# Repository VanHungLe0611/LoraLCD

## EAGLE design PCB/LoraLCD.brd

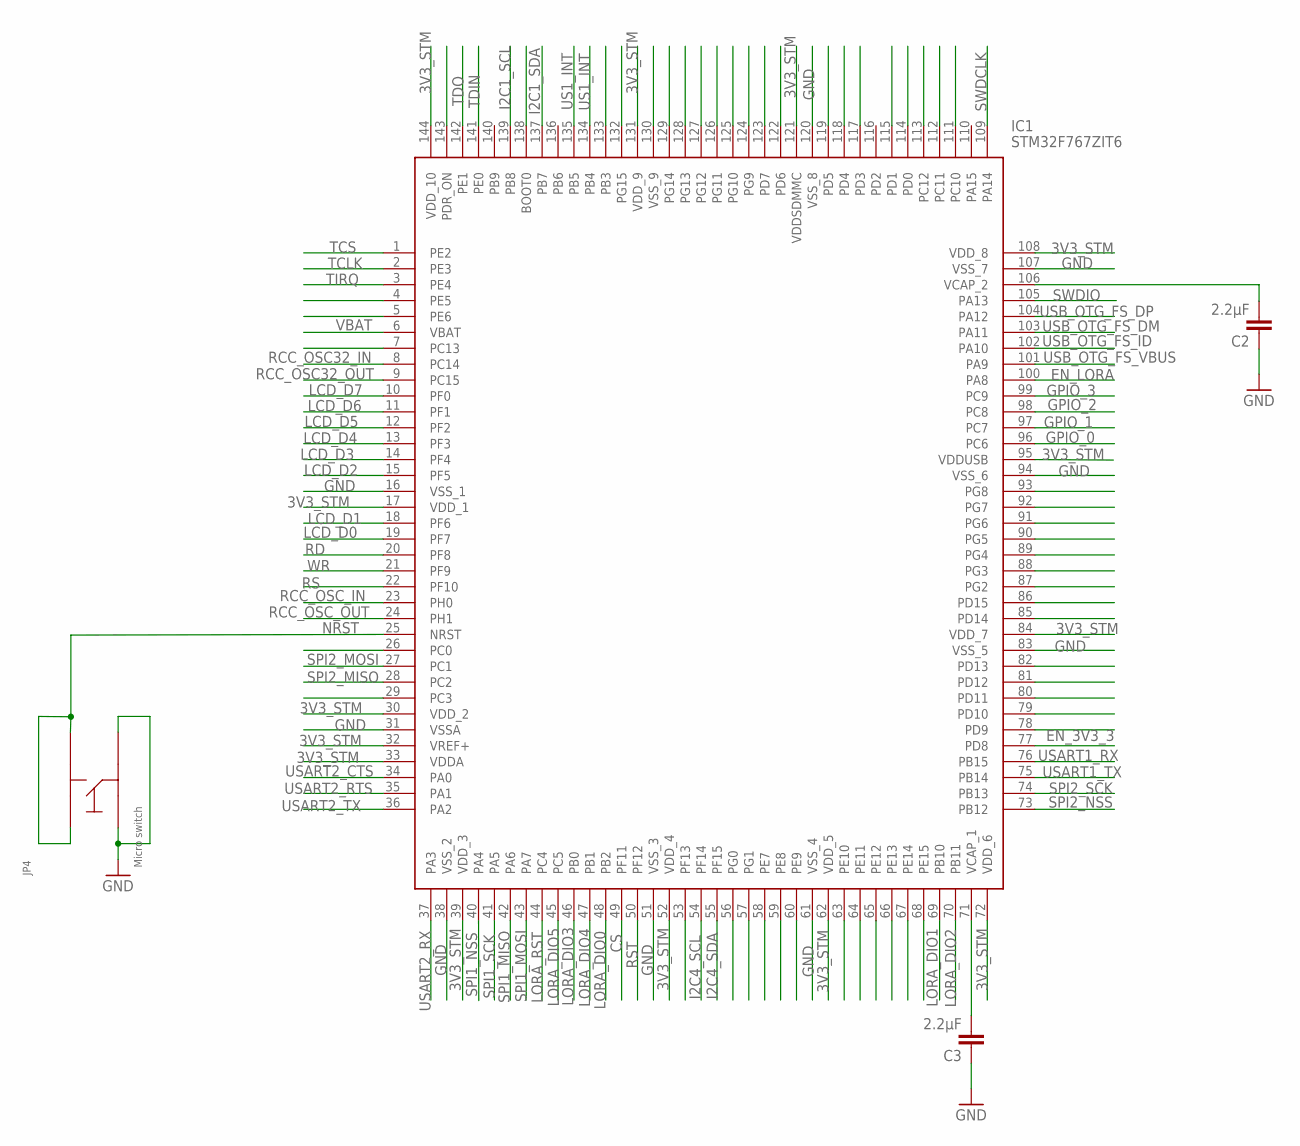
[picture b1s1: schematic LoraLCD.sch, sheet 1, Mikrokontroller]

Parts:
C2, C3: 2.2µF; C0402K
IC1: STM32F767ZIT6; QFP50P2200X2200X160-144N
JP4: MICRO_SWITCH_6MM; SKQGADE010; MPN SKQGADE010

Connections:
3V3_STM: IC1.17 (VDD_1), IC1.30 (VDD_2), IC1.32 (VREF+), IC1.33 (VDDA), IC1.39 (VDD_3), IC1.52 (VDD_4), IC1.62 (VDD_5), IC1.72 (VDD_6), IC1.84 (VDD_7), IC1.95 (VDDUSB), IC1.108 (VDD_8), IC1.121 (VDDSDMMC), IC1.131 (VDD_9), IC1.144 (VDD_10); also elsewhere on the board
CS: IC1.49 (PF11); also elsewhere on the board
EN_3V3_3: IC1.77 (PD8); also elsewhere on the board
EN_LORA: IC1.100 (PA8); also elsewhere on the board
GND: C2.1, C3.1, IC1.16 (VSS_1), IC1.31 (VSSA), IC1.38 (VSS_2), IC1.51 (VSS_3), IC1.61 (VSS_4), IC1.83 (VSS_5), IC1.94 (VSS_6), IC1.107 (VSS_7), IC1.120 (VSS_8), JP4.P$3, JP4.P$4; also elsewhere on the board
GPIO_0: IC1.96 (PC6); also elsewhere on the board
GPIO_1: IC1.97 (PC7); also elsewhere on the board
GPIO_2: IC1.98 (PC8); also elsewhere on the board
GPIO_3: IC1.99 (PC9); also elsewhere on the board
I2C1_SCL: IC1.139 (PB8); also elsewhere on the board
I2C1_SDA: IC1.137 (PB7); also elsewhere on the board
I2C4_SCL: IC1.54 (PF14); also elsewhere on the board
I2C4_SDA: IC1.55 (PF15); also elsewhere on the board
LCD_D0: IC1.19 (PF7); also elsewhere on the board
LCD_D1: IC1.18 (PF6); also elsewhere on the board
LCD_D2: IC1.15 (PF5); also elsewhere on the board
LCD_D3: IC1.14 (PF4); also elsewhere on the board
LCD_D4: IC1.13 (PF3); also elsewhere on the board
LCD_D5: IC1.12 (PF2); also elsewhere on the board
LCD_D6: IC1.11 (PF1); also elsewhere on the board
LCD_D7: IC1.10 (PF0); also elsewhere on the board
LORA_DIO0: IC1.48 (PB2); also elsewhere on the board
LORA_DIO1: IC1.69 (PB10); also elsewhere on the board
LORA_DIO2: IC1.70 (PB11); also elsewhere on the board
LORA_DIO3: IC1.46 (PB0); also elsewhere on the board
LORA_DIO4: IC1.47 (PB1); also elsewhere on the board
LORA_DIO5: IC1.45 (PC5); also elsewhere on the board
LORA_RST: IC1.44 (PC4); also elsewhere on the board
unnamed: C2.2, IC1.106 (VCAP_2)
unnamed: C3.2, IC1.71 (VCAP_1)
NRST: IC1.25 (NRST), JP4.P$1, JP4.P$2; also elsewhere on the board
RCC_OSC32_IN: IC1.8 (PC14); also elsewhere on the board
RCC_OSC32_OUT: IC1.9 (PC15); also elsewhere on the board
RCC_OSC_IN: IC1.23 (PH0); also elsewhere on the board
RCC_OSC_OUT: IC1.24 (PH1); also elsewhere on the board
RD: IC1.20 (PF8); also elsewhere on the board
RS: IC1.22 (PF10); also elsewhere on the board
RST: IC1.50 (PF12); also elsewhere on the board
SPI1_MISO: IC1.42 (PA6); also elsewhere on the board
SPI1_MOSI: IC1.43 (PA7); also elsewhere on the board
SPI1_NSS: IC1.40 (PA4); also elsewhere on the board
SPI1_SCK: IC1.41 (PA5); also elsewhere on the board
SPI2_MISO: IC1.28 (PC2); also elsewhere on the board
SPI2_MOSI: IC1.27 (PC1); also elsewhere on the board
SPI2_NSS: IC1.73 (PB12); also elsewhere on the board
SPI2_SCK: IC1.74 (PB13); also elsewhere on the board
SWDCLK: IC1.109 (PA14); also elsewhere on the board
SWDIO: IC1.105 (PA13); also elsewhere on the board
TCLK: IC1.2 (PE3); also elsewhere on the board
TCS: IC1.1 (PE2); also elsewhere on the board
TDIN: IC1.141 (PE0); also elsewhere on the board
TDO: IC1.142 (PE1); also elsewhere on the board
TIRQ: IC1.3 (PE4); also elsewhere on the board
US1_INT: IC1.134 (PB4), IC1.135 (PB5); also elsewhere on the board
USART1_RX: IC1.76 (PB15); also elsewhere on the board
USART1_TX: IC1.75 (PB14); also elsewhere on the board
USART2_CTS: IC1.34 (PA0); also elsewhere on the board
USART2_RTS: IC1.35 (PA1); also elsewhere on the board
USART2_RX: IC1.37 (PA3); also elsewhere on the board
USART2_TX: IC1.36 (PA2); also elsewhere on the board
USB_OTG_FS_DM: IC1.103 (PA11); also elsewhere on the board
USB_OTG_FS_DP: IC1.104 (PA12); also elsewhere on the board
USB_OTG_FS_ID: IC1.102 (PA10); also elsewhere on the board
USB_OTG_FS_VBUS: IC1.101 (PA9); also elsewhere on the board
VBAT: IC1.6 (VBAT); also elsewhere on the board
WR: IC1.21 (PF9); also elsewhere on the board

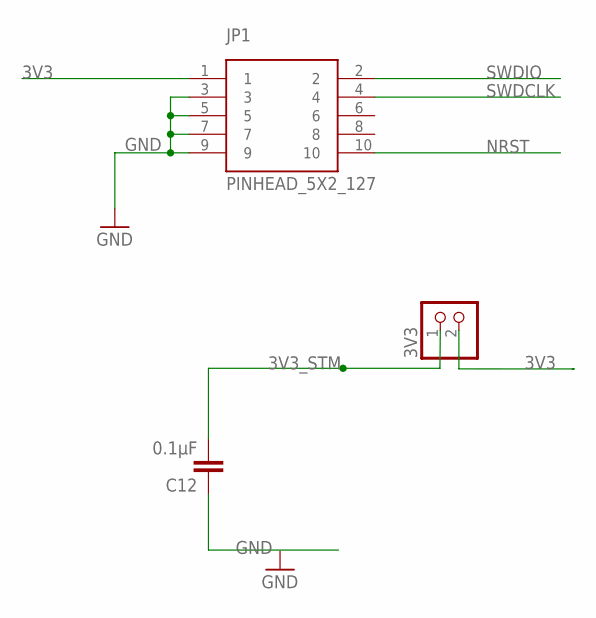
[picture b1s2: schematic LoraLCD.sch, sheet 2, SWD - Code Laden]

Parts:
3V3: PINHD-1X2; 1X02
C12: 0.1µF; C0402K
JP1: PINHEAD_5X2_127; PINHEAD_2X5_127

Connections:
3V3: 3V3.2, JP1.1; also elsewhere on the board
3V3_STM: 3V3.1, C12.2; also elsewhere on the board
GND: C12.1, JP1.3, JP1.5, JP1.7, JP1.9; also elsewhere on the board
NRST: JP1.10; also elsewhere on the board
SWDCLK: JP1.4; also elsewhere on the board
SWDIO: JP1.2; also elsewhere on the board

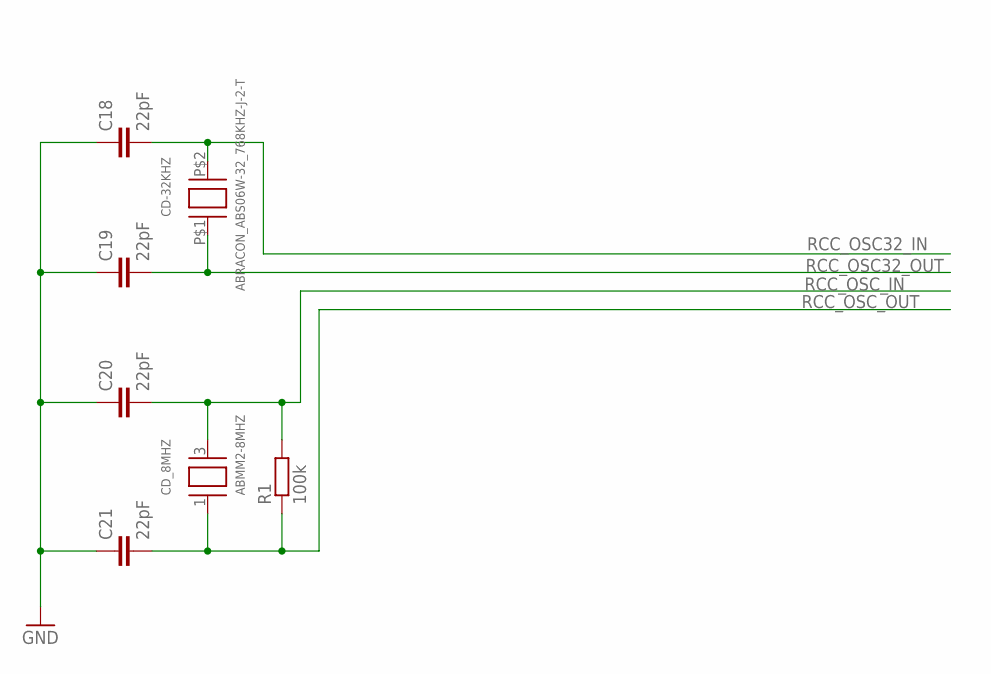
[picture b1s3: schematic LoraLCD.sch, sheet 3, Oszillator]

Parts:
C18, C19, C20, C21: 22pF; C0402K
CD-32KHZ: ABRACON_ABS06W-32_768KHZ-J-2-T; 2MM_X_1_2MM
CD_8MHZ: ABMM2-8MHZ; CRYSTAL_ABRACON_6MM_3.6MM
R1: 100k; C0402K

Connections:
GND: C18.1, C19.1, C20.1, C21.1; also elsewhere on the board
RCC_OSC32_IN: C18.2, CD-32KHZ.P$2 (C1); also elsewhere on the board
RCC_OSC32_OUT: C19.2, CD-32KHZ.P$1 (C0); also elsewhere on the board
RCC_OSC_IN: C20.2, CD_8MHZ.3 (C1), R1.2; also elsewhere on the board
RCC_OSC_OUT: C21.2, CD_8MHZ.1 (C0), R1.1; also elsewhere on the board

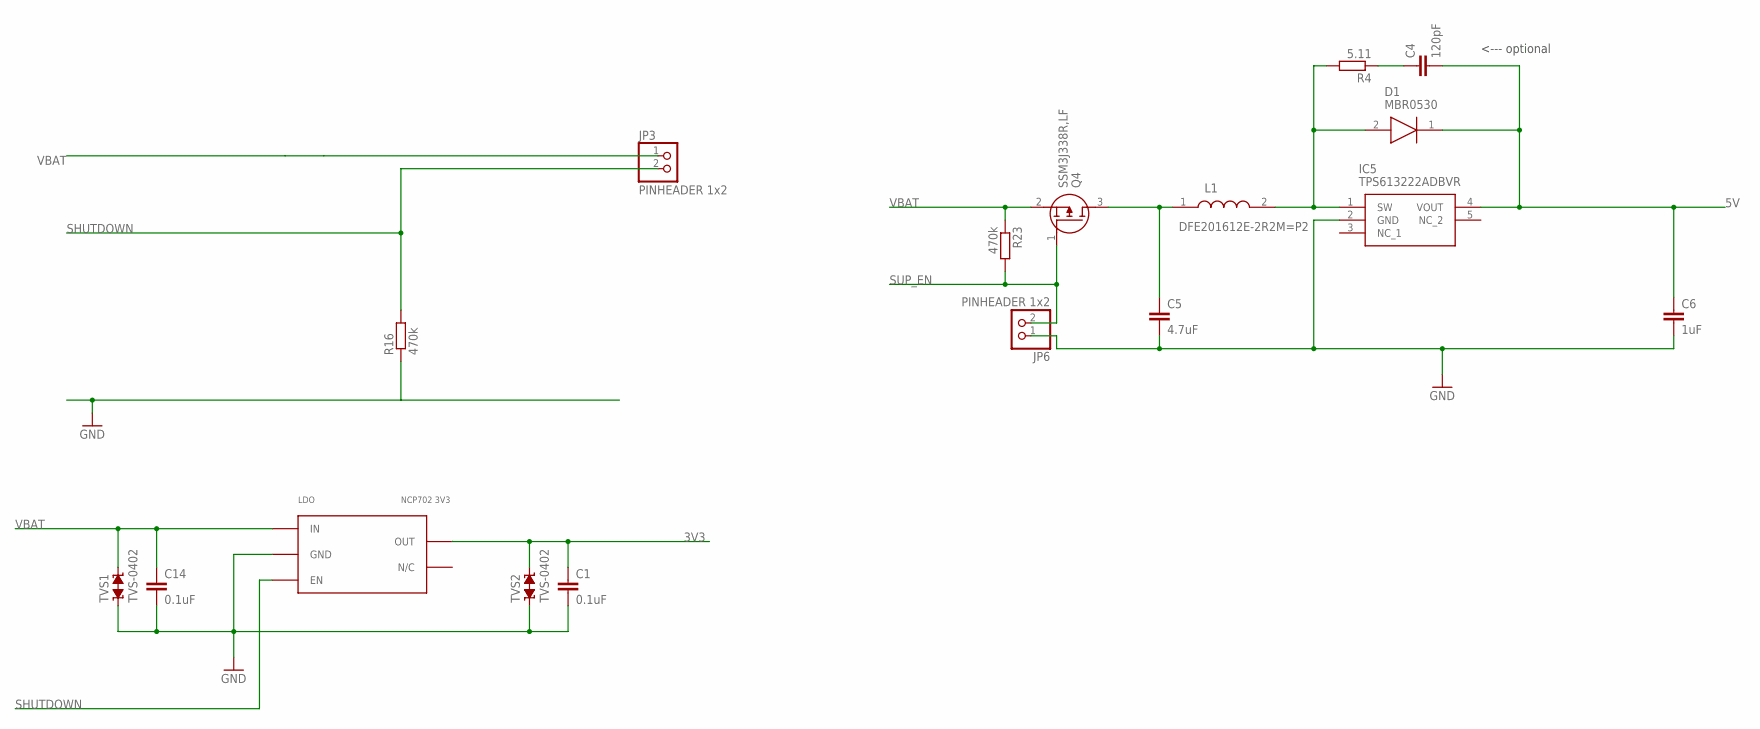
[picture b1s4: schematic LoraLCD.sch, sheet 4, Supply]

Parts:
C1: 0.1uF; C0402K; MPN CCC-23
C4: 120pF; C0402K; MPN GRM1555C1H121JA01D
C5: 4.7uF; C0603K; MPN JMK107BB7475KA-T
C6: 1uF; C0603K
C14: 0.1uF; C0402K
D1: MBR0530; SOD3716X135N
IC5: TPS613222ADBVR; SOT95P280X145-5N
JP3, JP6: PINHEADER 1x2; 1X02
L1: DFE201612E-2R2M=P2; INDC2016X120N
LDO: NCP702 3V3; SOT563; MPN NCP702SN33T1G
Q4: SSM3J338R,LF; SSM3J332RLFT
R4: 5.11; R0402; MPN RC0402FR-132M2L
R16, R23: 470k; R0402
TVS1, TVS2: TVS-0402; TVS0402; MPN PESD0402-140

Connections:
3V3: C1.1, LDO.P$5 (OUT), TVS2.2; also elsewhere on the board
5V: C4.2, C6.1, D1.1 (K), IC5.4 (VOUT); also elsewhere on the board
GND: C1.2, C5.2, C6.2, C14.2, IC5.2 (GND), JP6.1, LDO.P$2 (GND), R16.1, TVS1.1, TVS2.1; also elsewhere on the board
unnamed: D1.2 (A), IC5.1 (SW), L1.2, R4.2
unnamed: C4.1, R4.1
unnamed: C5.1, L1.1, Q4.3 (D)
SHUTDOWN: JP3.2, LDO.P$3 (EN), R16.2
SUP_EN: JP6.2, Q4.1 (G), R23.2
VBAT: C14.1, JP3.1, LDO.P$1 (IN), Q4.2 (S), R23.1, TVS1.2; also elsewhere on the board

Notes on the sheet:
<--- optional

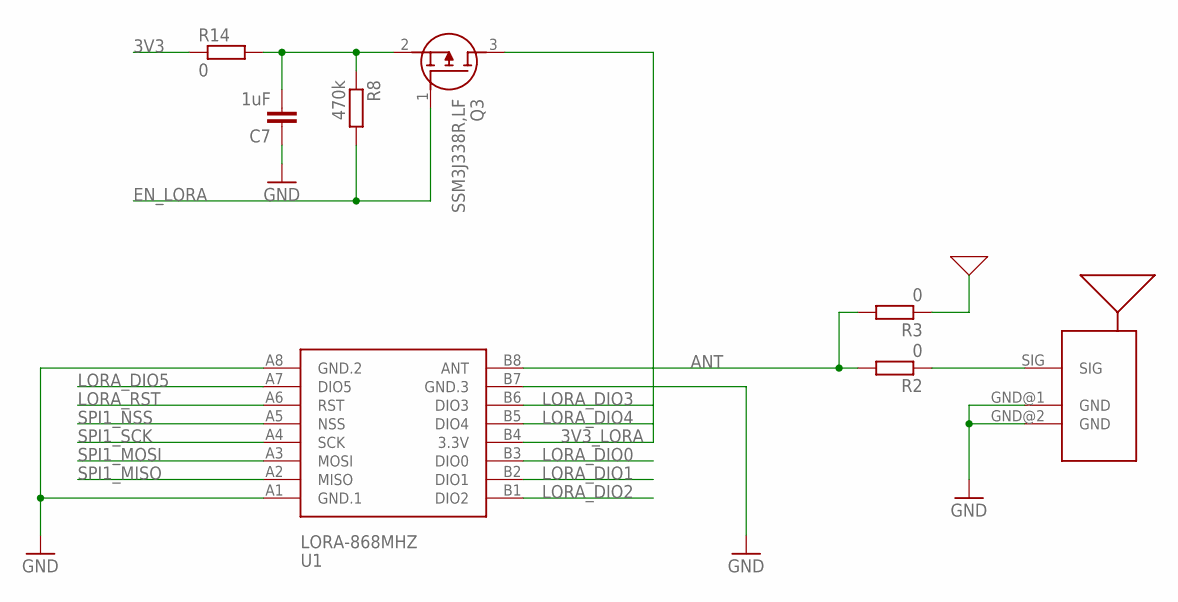
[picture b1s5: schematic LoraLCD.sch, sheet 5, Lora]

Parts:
ANT1: U.FL-R-SMT-1; UFL_HIROSE; MPN U.FL-R-SMT-1(10)
C7: 1uF; C0402K
Q3: SSM3J338R,LF; SSM3J332RLFT
R2, R3: 0; C0402K
R8: 470k; R0402
R14: 0; R0402
U1: LORA-868MHZ; WIRELESS-LORA-RFM95W#SMD

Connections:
3V3: R14.1; also elsewhere on the board
3V3_LORA: Q3.3 (D), U1.B4 (3.3V)
ANT: R2.2, R3.2, U1.B8 (ANT)
EN_LORA: Q3.1 (G), R8.2; also elsewhere on the board
GND: ANT1.GND@1 (GND), ANT1.GND@2 (GND), C7.1, U1.A1 (GND.1), U1.A8 (GND.2), U1.B7 (GND.3); also elsewhere on the board
HELIX_ANT: R3.1
LORA_DIO0: U1.B3 (DIO0); also elsewhere on the board
LORA_DIO1: U1.B2 (DIO1); also elsewhere on the board
LORA_DIO2: U1.B1 (DIO2); also elsewhere on the board
LORA_DIO3: U1.B6 (DIO3); also elsewhere on the board
LORA_DIO4: U1.B5 (DIO4); also elsewhere on the board
LORA_DIO5: U1.A7 (DIO5); also elsewhere on the board
LORA_RST: U1.A6 (RST); also elsewhere on the board
unnamed: ANT1.SIG, R2.1
unnamed: C7.2, Q3.2 (S), R8.1, R14.2
SPI1_MISO: U1.A2 (MISO); also elsewhere on the board
SPI1_MOSI: U1.A3 (MOSI); also elsewhere on the board
SPI1_NSS: U1.A5 (NSS); also elsewhere on the board
SPI1_SCK: U1.A4 (SCK); also elsewhere on the board

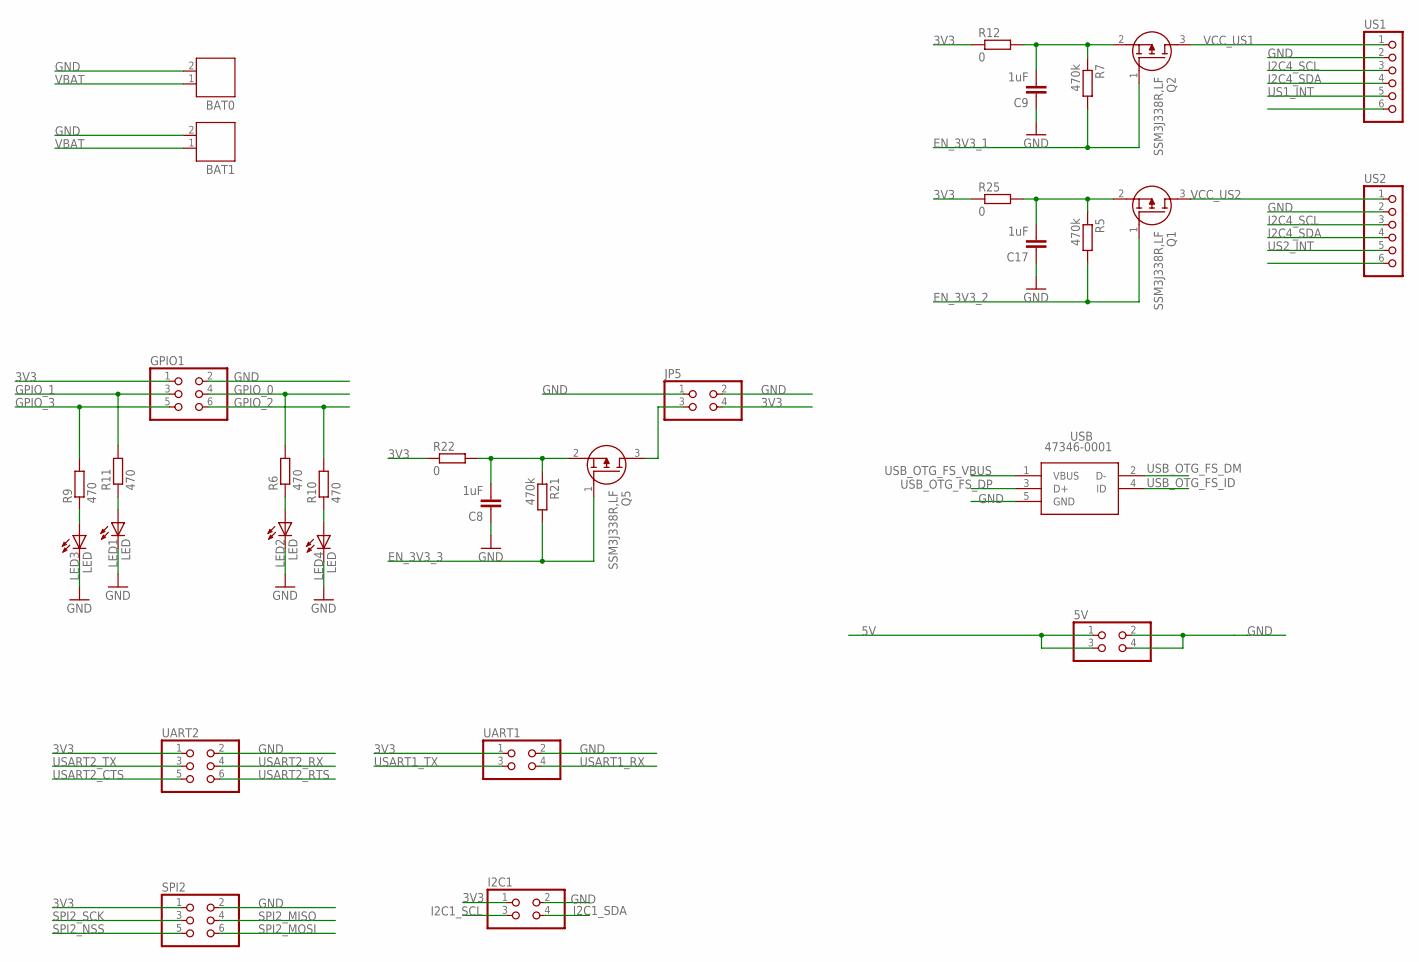
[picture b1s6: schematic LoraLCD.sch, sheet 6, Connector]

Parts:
5V: PINHD-2X2; 2X02
BAT0, BAT1: JST-PH2; MPN B2B-PH-K-S
C8, C9, C17: 1uF; C0402K
GPIO1: PINHD-2X3; 2X03
I2C1: PINHD-2X2; 2X02
JP5: PINHD-2X2; 2X02
LED1, LED2, LED3, LED4: LED; 0603_AK
Q1, Q2, Q5: SSM3J338R,LF; SSM3J332RLFT
R5, R7, R21: 470k; R0402
R6, R9, R10, R11: 470; R0402
R12, R22, R25: 0; R0402
SPI2: PINHD-2X3; 2X03
UART1: PINHD-2X2; 2X02
UART2: PINHD-2X3; 2X03
US1, US2: PINHD-1X6; 1X06
USB: 47346-0001

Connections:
3V3: GPIO1.1, I2C1.1, JP5.4, R12.1, R22.1, R25.1, SPI2.1, UART1.1, UART2.1; also elsewhere on the board
5V: 5V.1, 5V.3; also elsewhere on the board
EN_3V3_1: Q2.1 (G), R7.2
EN_3V3_2: Q1.1 (G), R5.2
EN_3V3_3: Q5.1 (G), R21.2; also elsewhere on the board
GND: 5V.2, 5V.4, BAT0.2, BAT1.2, C8.1, C9.1, C17.1, GPIO1.2, I2C1.2, JP5.1, JP5.2, LED1.K (C), LED2.K (C), LED3.K (C), LED4.K (C), SPI2.2, UART1.2, UART2.2, US1.2, US2.2, USB.5 (GND); also elsewhere on the board
GPIO_0: GPIO1.4, R6.2; also elsewhere on the board
GPIO_1: GPIO1.3, R11.2; also elsewhere on the board
GPIO_2: GPIO1.6, R10.2; also elsewhere on the board
GPIO_3: GPIO1.5, R9.2; also elsewhere on the board
I2C1_SCL: I2C1.3; also elsewhere on the board
I2C1_SDA: I2C1.4; also elsewhere on the board
I2C4_SCL: US1.3, US2.3; also elsewhere on the board
I2C4_SDA: US1.4, US2.4; also elsewhere on the board
unnamed: LED1.A, R11.1
unnamed: LED2.A, R6.1
unnamed: C17.2, Q1.2 (S), R5.1, R25.2
unnamed: LED3.A, R9.1
unnamed: LED4.A, R10.1
unnamed: C8.2, Q5.2 (S), R21.1, R22.2
unnamed: JP5.3, Q5.3 (D)
unnamed: C9.2, Q2.2 (S), R7.1, R12.2
PS: US1.6
SPI2_MISO: SPI2.4; also elsewhere on the board
SPI2_MOSI: SPI2.6; also elsewhere on the board
SPI2_NSS: SPI2.5; also elsewhere on the board
SPI2_SCK: SPI2.3; also elsewhere on the board
US1_INT: US1.5; also elsewhere on the board
US2_INT: US2.5
USART1_RX: UART1.4; also elsewhere on the board
USART1_TX: UART1.3; also elsewhere on the board
USART2_CTS: UART2.5; also elsewhere on the board
USART2_RTS: UART2.6; also elsewhere on the board
USART2_RX: UART2.4; also elsewhere on the board
USART2_TX: UART2.3; also elsewhere on the board
USB_OTG_FS_DM: USB.2 (D-); also elsewhere on the board
USB_OTG_FS_DP: USB.3 (D+); also elsewhere on the board
USB_OTG_FS_ID: USB.4 (ID); also elsewhere on the board
USB_OTG_FS_VBUS: USB.1 (VBUS); also elsewhere on the board
VBAT: BAT0.1, BAT1.1; also elsewhere on the board
VCC_US1: Q2.3 (D), US1.1
VCC_US2: Q1.3 (D), US2.1

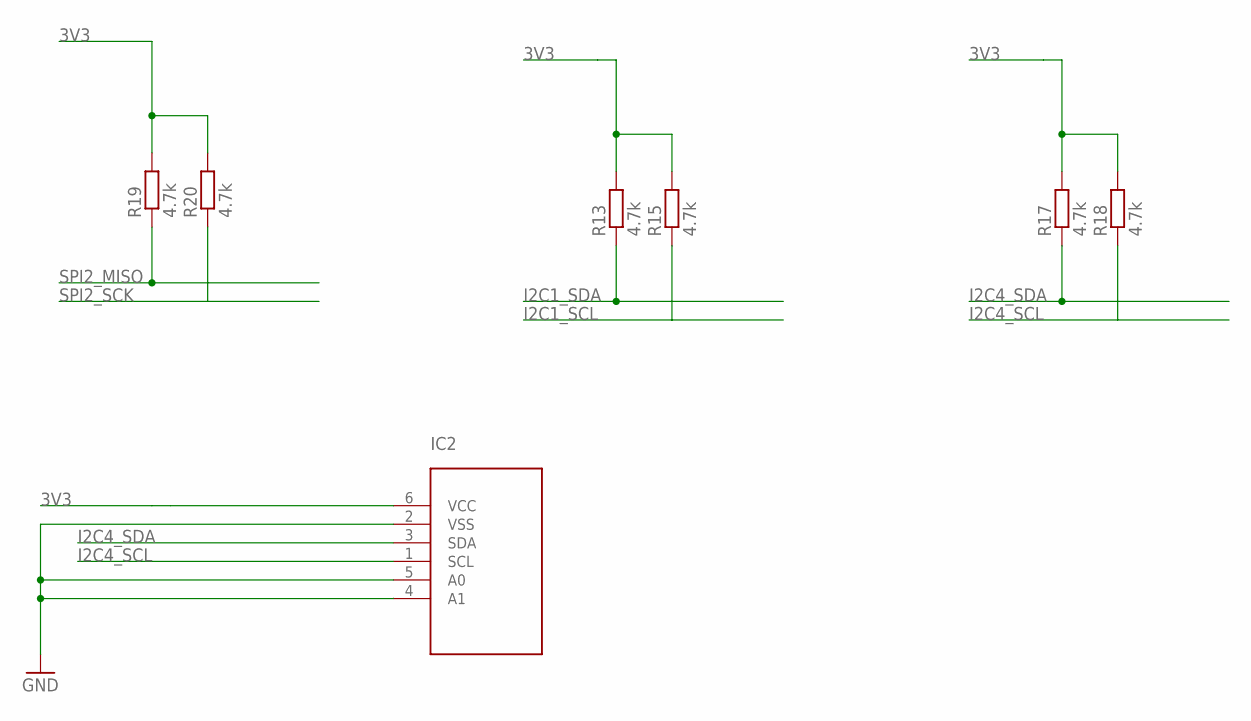
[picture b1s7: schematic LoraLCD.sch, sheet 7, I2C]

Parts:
IC2: 24AA025E64T-I/OT; SOT23-6; MPN 24AA025E64T-I/OT
R13, R15, R17, R18, R19, R20: 4.7k; C0402K

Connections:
3V3: IC2.6 (VCC), R13.2, R15.2, R17.2, R18.2, R19.2, R20.2; also elsewhere on the board
GND: IC2.2 (VSS), IC2.4 (A1), IC2.5 (A0); also elsewhere on the board
I2C1_SCL: R15.1; also elsewhere on the board
I2C1_SDA: R13.1; also elsewhere on the board
I2C4_SCL: IC2.1 (SCL), R18.1; also elsewhere on the board
I2C4_SDA: IC2.3 (SDA), R17.1; also elsewhere on the board
SPI2_MISO: R19.1; also elsewhere on the board
SPI2_SCK: R20.1; also elsewhere on the board

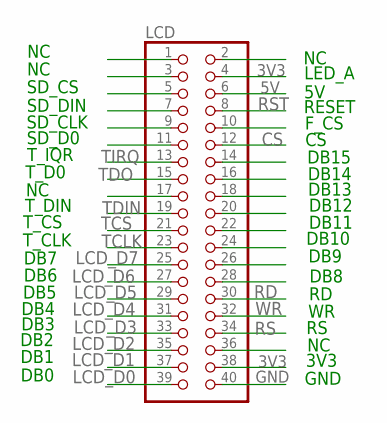
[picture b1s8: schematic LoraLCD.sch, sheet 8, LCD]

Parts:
LCD: PINHD-2X20; 2X20

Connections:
3V3: LCD.4, LCD.38; also elsewhere on the board
5V: LCD.6; also elsewhere on the board
CS: LCD.12; also elsewhere on the board
GND: LCD.40; also elsewhere on the board
LCD_D0: LCD.39; also elsewhere on the board
LCD_D1: LCD.37; also elsewhere on the board
LCD_D2: LCD.35; also elsewhere on the board
LCD_D3: LCD.33; also elsewhere on the board
LCD_D4: LCD.31; also elsewhere on the board
LCD_D5: LCD.29; also elsewhere on the board
LCD_D6: LCD.27; also elsewhere on the board
LCD_D7: LCD.25; also elsewhere on the board
RD: LCD.30; also elsewhere on the board
RS: LCD.34; also elsewhere on the board
RST: LCD.8; also elsewhere on the board
TCLK: LCD.23; also elsewhere on the board
TCS: LCD.21; also elsewhere on the board
TDIN: LCD.19; also elsewhere on the board
TDO: LCD.15; also elsewhere on the board
TIRQ: LCD.13; also elsewhere on the board
WR: LCD.32; also elsewhere on the board

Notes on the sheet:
LED_A
RESET
F_CS
DB15
DB14
DB13
DB12
DB11
DB10
DB9
DB8
3V3
GND
SD_CS
SD_DIN
SD_CLK
SD_D0
T_IQR
T_D0
T_DIN
T_CS
T_CLK
DB7
DB6
DB5
DB4
DB3
DB2
DB1
DB0

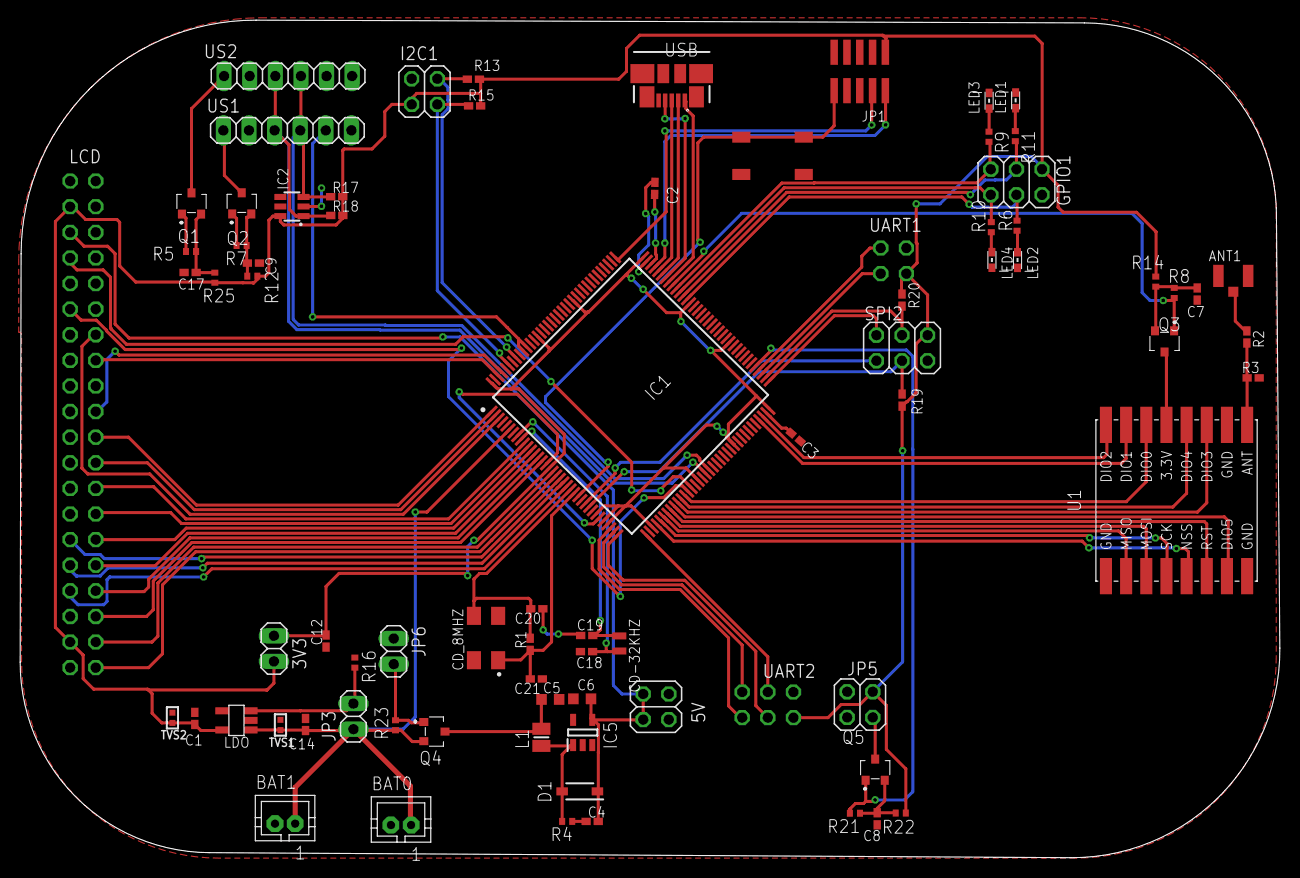
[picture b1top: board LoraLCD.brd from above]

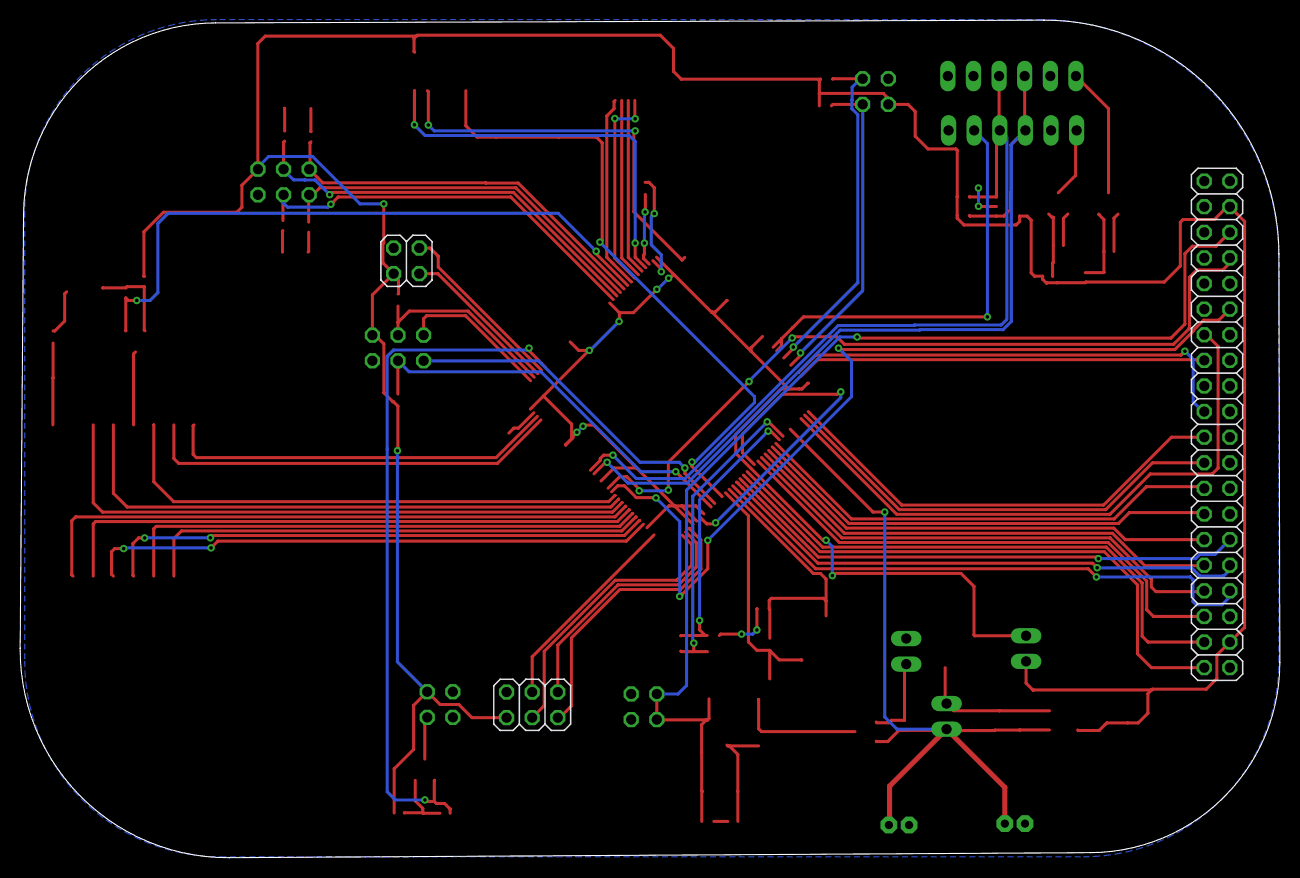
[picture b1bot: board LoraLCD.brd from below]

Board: 2 copper layers, 124.9 x 83.1 mm, 79 parts (3 on the bottom side), 89 nets.

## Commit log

2020-03-22 stm32f7 with lcd and lora modul
2020-03-27 fix 2 pin CS and RTS in control pin for LCD

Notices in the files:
parts and their libraries:
supressor: Copyright (C) 2009, Bob Starr
diy-modules: Released under the Creative Commons Attribution 4.0 International License: http://creativecommons.org/licenses/by/4.0
